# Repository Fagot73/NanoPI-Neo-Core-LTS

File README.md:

# NanoPI-Core-LTS

The first attempt to create a 3D model of the CPU board FriendlyElec NanoPI NEO Core

- processor: H3 
- KiCad libs
- STEP model

Dimensions from manual and checked by NanoPi_NEO_Core-1_0_1705_Dimensions.dxf .

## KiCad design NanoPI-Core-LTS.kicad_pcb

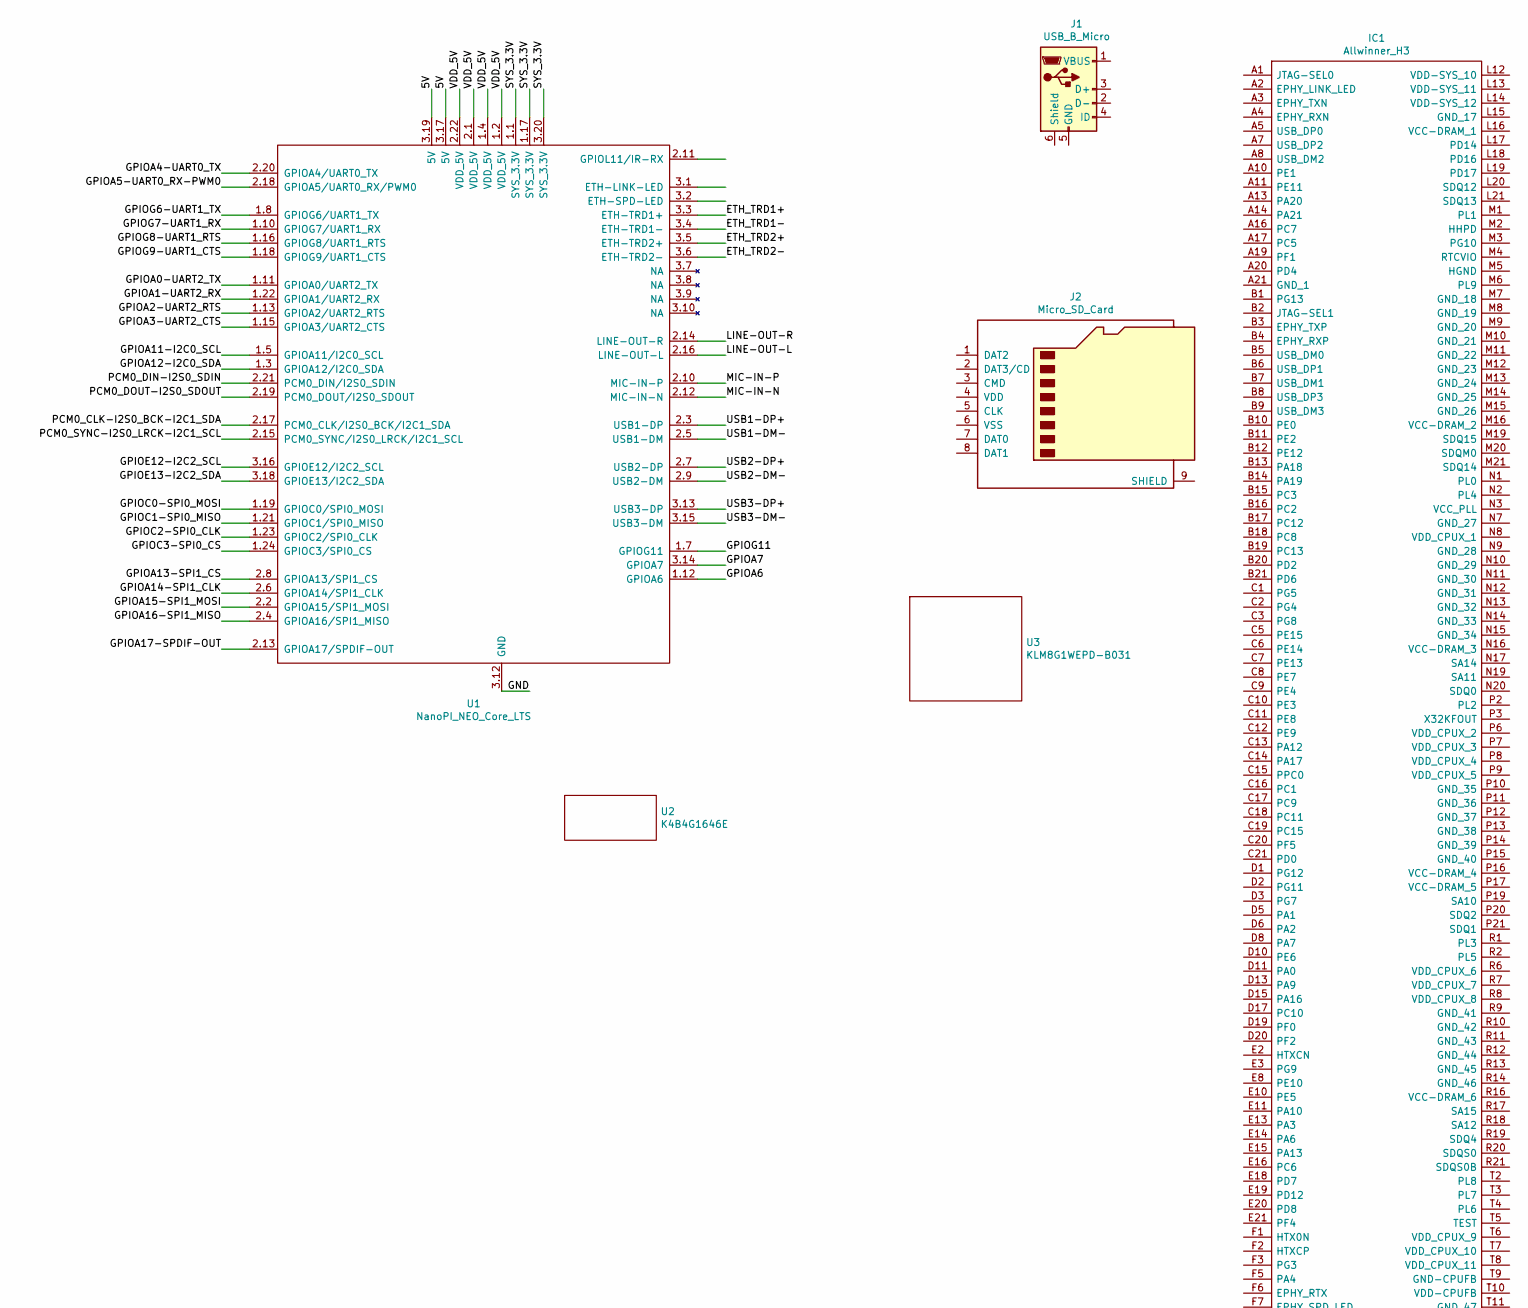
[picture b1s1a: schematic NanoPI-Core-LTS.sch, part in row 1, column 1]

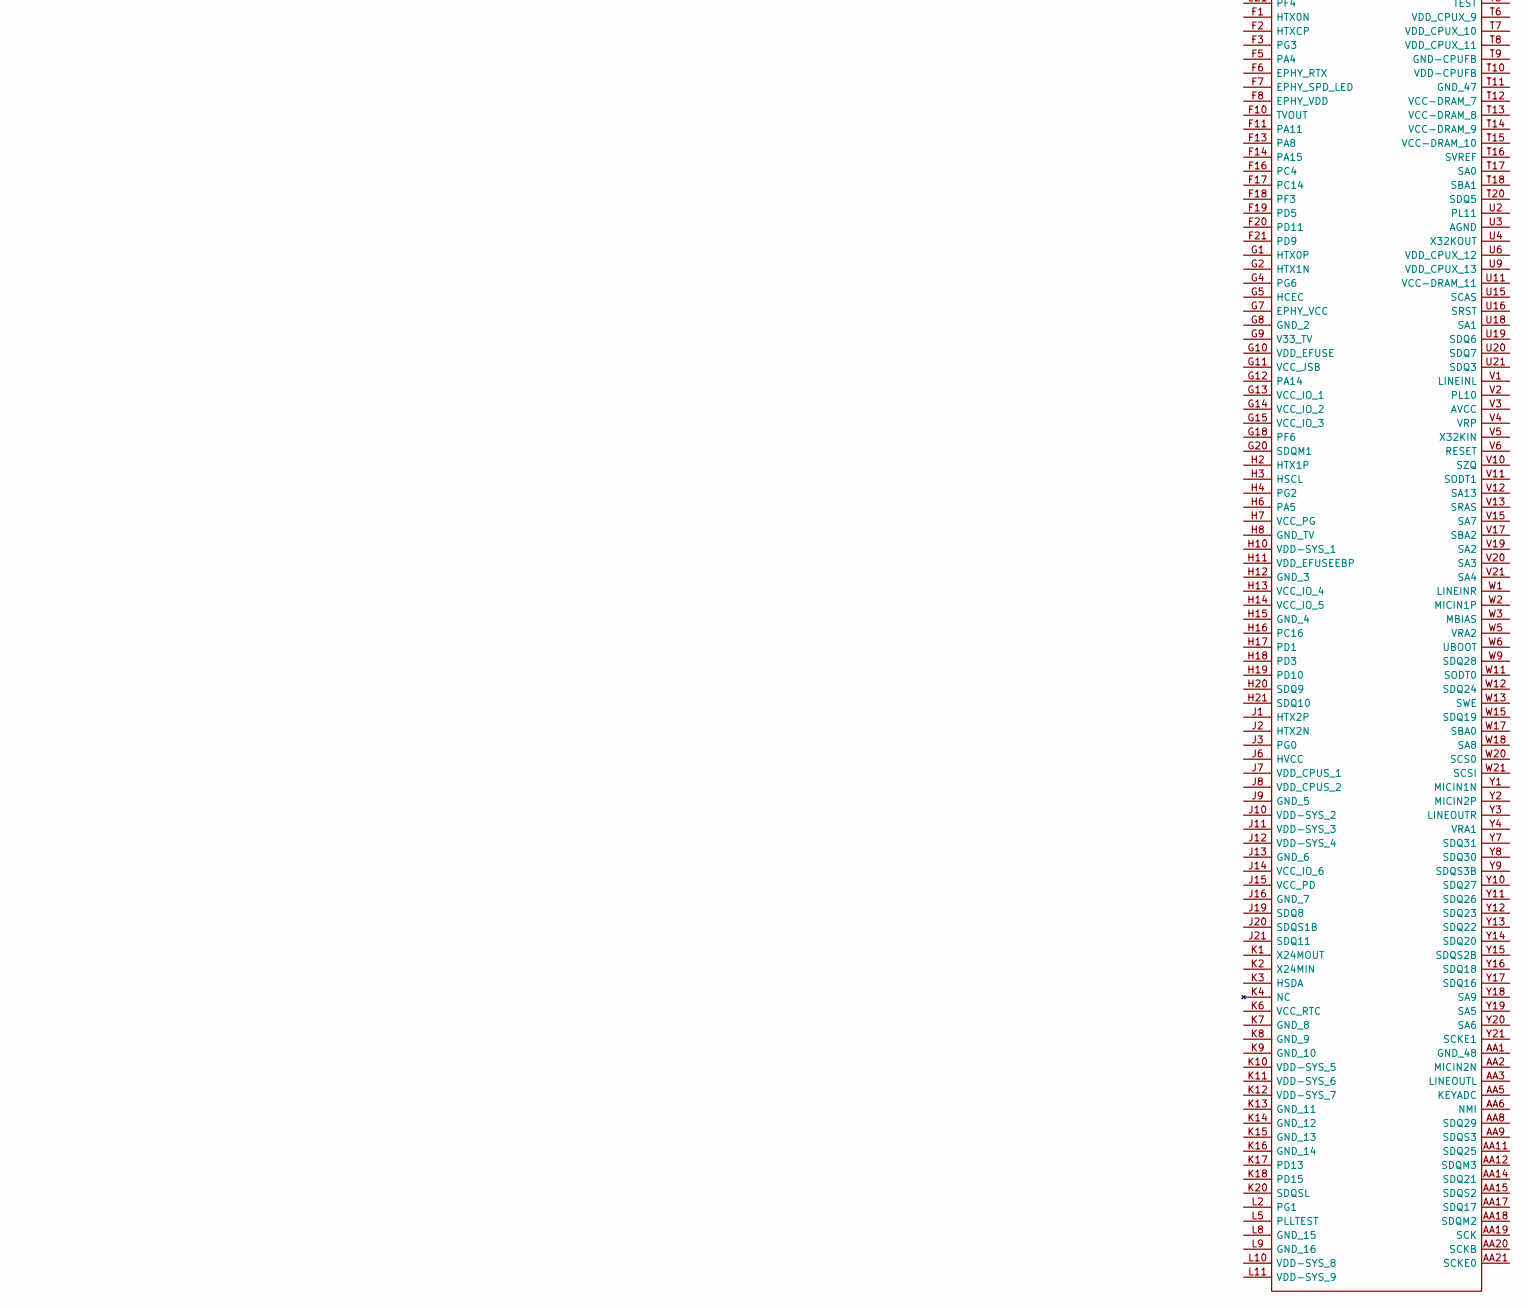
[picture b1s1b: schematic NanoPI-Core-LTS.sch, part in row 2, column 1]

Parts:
IC1: Allwinner_H3; BGA347C65P21X21_1400X1400X118; Manufacturer_Part_Number Allwinner H3
J1: USB_B_Micro; USB_Micro-B_Molex-105017-0001
J2: Micro_SD_Card; sdcard-from-nanopi_core
U1: NanoPI_NEO_Core_LTS; NanoPI_NEO_Core_LTS_Canonical
U2: K4B4G1646E
U3: KLM8G1WEPD-B031

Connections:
/5V: U1.3.17 (5V), U1.3.19 (5V)
/ETH_TRD1+: U1.3.3 (ETH-TRD1+)
/ETH_TRD1-: U1.3.4 (ETH-TRD1-)
/ETH_TRD2+: U1.3.5 (ETH-TRD2+)
/ETH_TRD2-: U1.3.6 (ETH-TRD2-)
/GPIOA0-UART2_TX: U1.1.11 (GPIOA0/UART2_TX)
/GPIOA1-UART2_RX: U1.1.22 (GPIOA1/UART2_RX)
/GPIOA2-UART2_RTS: U1.1.13 (GPIOA2/UART2_RTS)
/GPIOA3-UART2_CTS: U1.1.15 (GPIOA3/UART2_CTS)
/GPIOA4-UART0_TX: U1.2.20 (GPIOA4/UART0_TX)
/GPIOA5-UART0_RX-PWM0: U1.2.18 (GPIOA5/UART0_RX/PWM0)
/GPIOA6: U1.1.12 (GPIOA6)
/GPIOA7: U1.3.14 (GPIOA7)
/GPIOA11-I2C0_SCL: U1.1.5 (GPIOA11/I2C0_SCL)
/GPIOA12-I2C0_SDA: U1.1.3 (GPIOA12/I2C0_SDA)
/GPIOA13-SPI1_CS: U1.2.8 (GPIOA13/SPI1_CS)
/GPIOA14-SPI1_CLK: U1.2.6 (GPIOA14/SPI1_CLK)
/GPIOA15-SPI1_MOSI: U1.2.2 (GPIOA15/SPI1_MOSI)
/GPIOA16-SPI1_MISO: U1.2.4 (GPIOA16/SPI1_MISO)
/GPIOA17-SPDIF-OUT: U1.2.13 (GPIOA17/SPDIF-OUT)
/GPIOC0-SPI0_MOSI: U1.1.19 (GPIOC0/SPI0_MOSI)
/GPIOC1-SPI0_MISO: U1.1.21 (GPIOC1/SPI0_MISO)
/GPIOC2-SPI0_CLK: U1.1.23 (GPIOC2/SPI0_CLK)
/GPIOC3-SPI0_CS: U1.1.24 (GPIOC3/SPI0_CS)
/GPIOE12-I2C2_SCL: U1.3.16 (GPIOE12/I2C2_SCL)
/GPIOE13-I2C2_SDA: U1.3.18 (GPIOE13/I2C2_SDA)
/GPIOG6-UART1_TX: U1.1.8 (GPIOG6/UART1_TX)
/GPIOG7-UART1_RX: U1.1.10 (GPIOG7/UART1_RX)
/GPIOG8-UART1_RTS: U1.1.16 (GPIOG8/UART1_RTS)
/GPIOG9-UART1_CTS: U1.1.18 (GPIOG9/UART1_CTS)
/GPIOG11: U1.1.7 (GPIOG11)
/LINE-OUT-L: U1.2.16 (LINE-OUT-L)
/LINE-OUT-R: U1.2.14 (LINE-OUT-R)
/MIC-IN-N: U1.2.12 (MIC-IN-N)
/MIC-IN-P: U1.2.10 (MIC-IN-P)
/PCM0_CLK-I2S0_BCK-I2C1_SDA: U1.2.17 (PCM0_CLK/I2S0_BCK/I2C1_SDA)
/PCM0_DIN-I2S0_SDIN: U1.2.21 (PCM0_DIN/I2S0_SDIN)
/PCM0_DOUT-I2S0_SDOUT: U1.2.19 (PCM0_DOUT/I2S0_SDOUT)
/PCM0_SYNC-I2S0_LRCK-I2C1_SCL: U1.2.15 (PCM0_SYNC/I2S0_LRCK/I2C1_SCL)
/SYS_3.3V: U1.1.1 (SYS_3.3V), U1.1.17 (SYS_3.3V), U1.3.20 (SYS_3.3V)
/USB1-DM-: U1.2.5 (USB1-DM)
/USB1-DP+: U1.2.3 (USB1-DP)
/USB2-DM-: U1.2.9 (USB2-DM)
/USB2-DP+: U1.2.7 (USB2-DP)
/USB3-DM-: U1.3.15 (USB3-DM)
/USB3-DP+: U1.3.13 (USB3-DP)
/VDD_5V: U1.1.2 (VDD_5V), U1.1.4 (VDD_5V), U1.2.1 (VDD_5V), U1.2.22 (VDD_5V)
GND: U1.1.6 (GND), U1.1.9 (GND), U1.1.14 (GND), U1.1.20 (GND), U1.2.23 (GND), U1.2.24 (GND), U1.3.11 (GND), U1.3.12 (GND)

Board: 2 copper layers, 6 parts (3 on the bottom side), 4 nets, no tracks yet.

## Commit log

2021-03-30 Initial import
2021-03-30 Add some images
